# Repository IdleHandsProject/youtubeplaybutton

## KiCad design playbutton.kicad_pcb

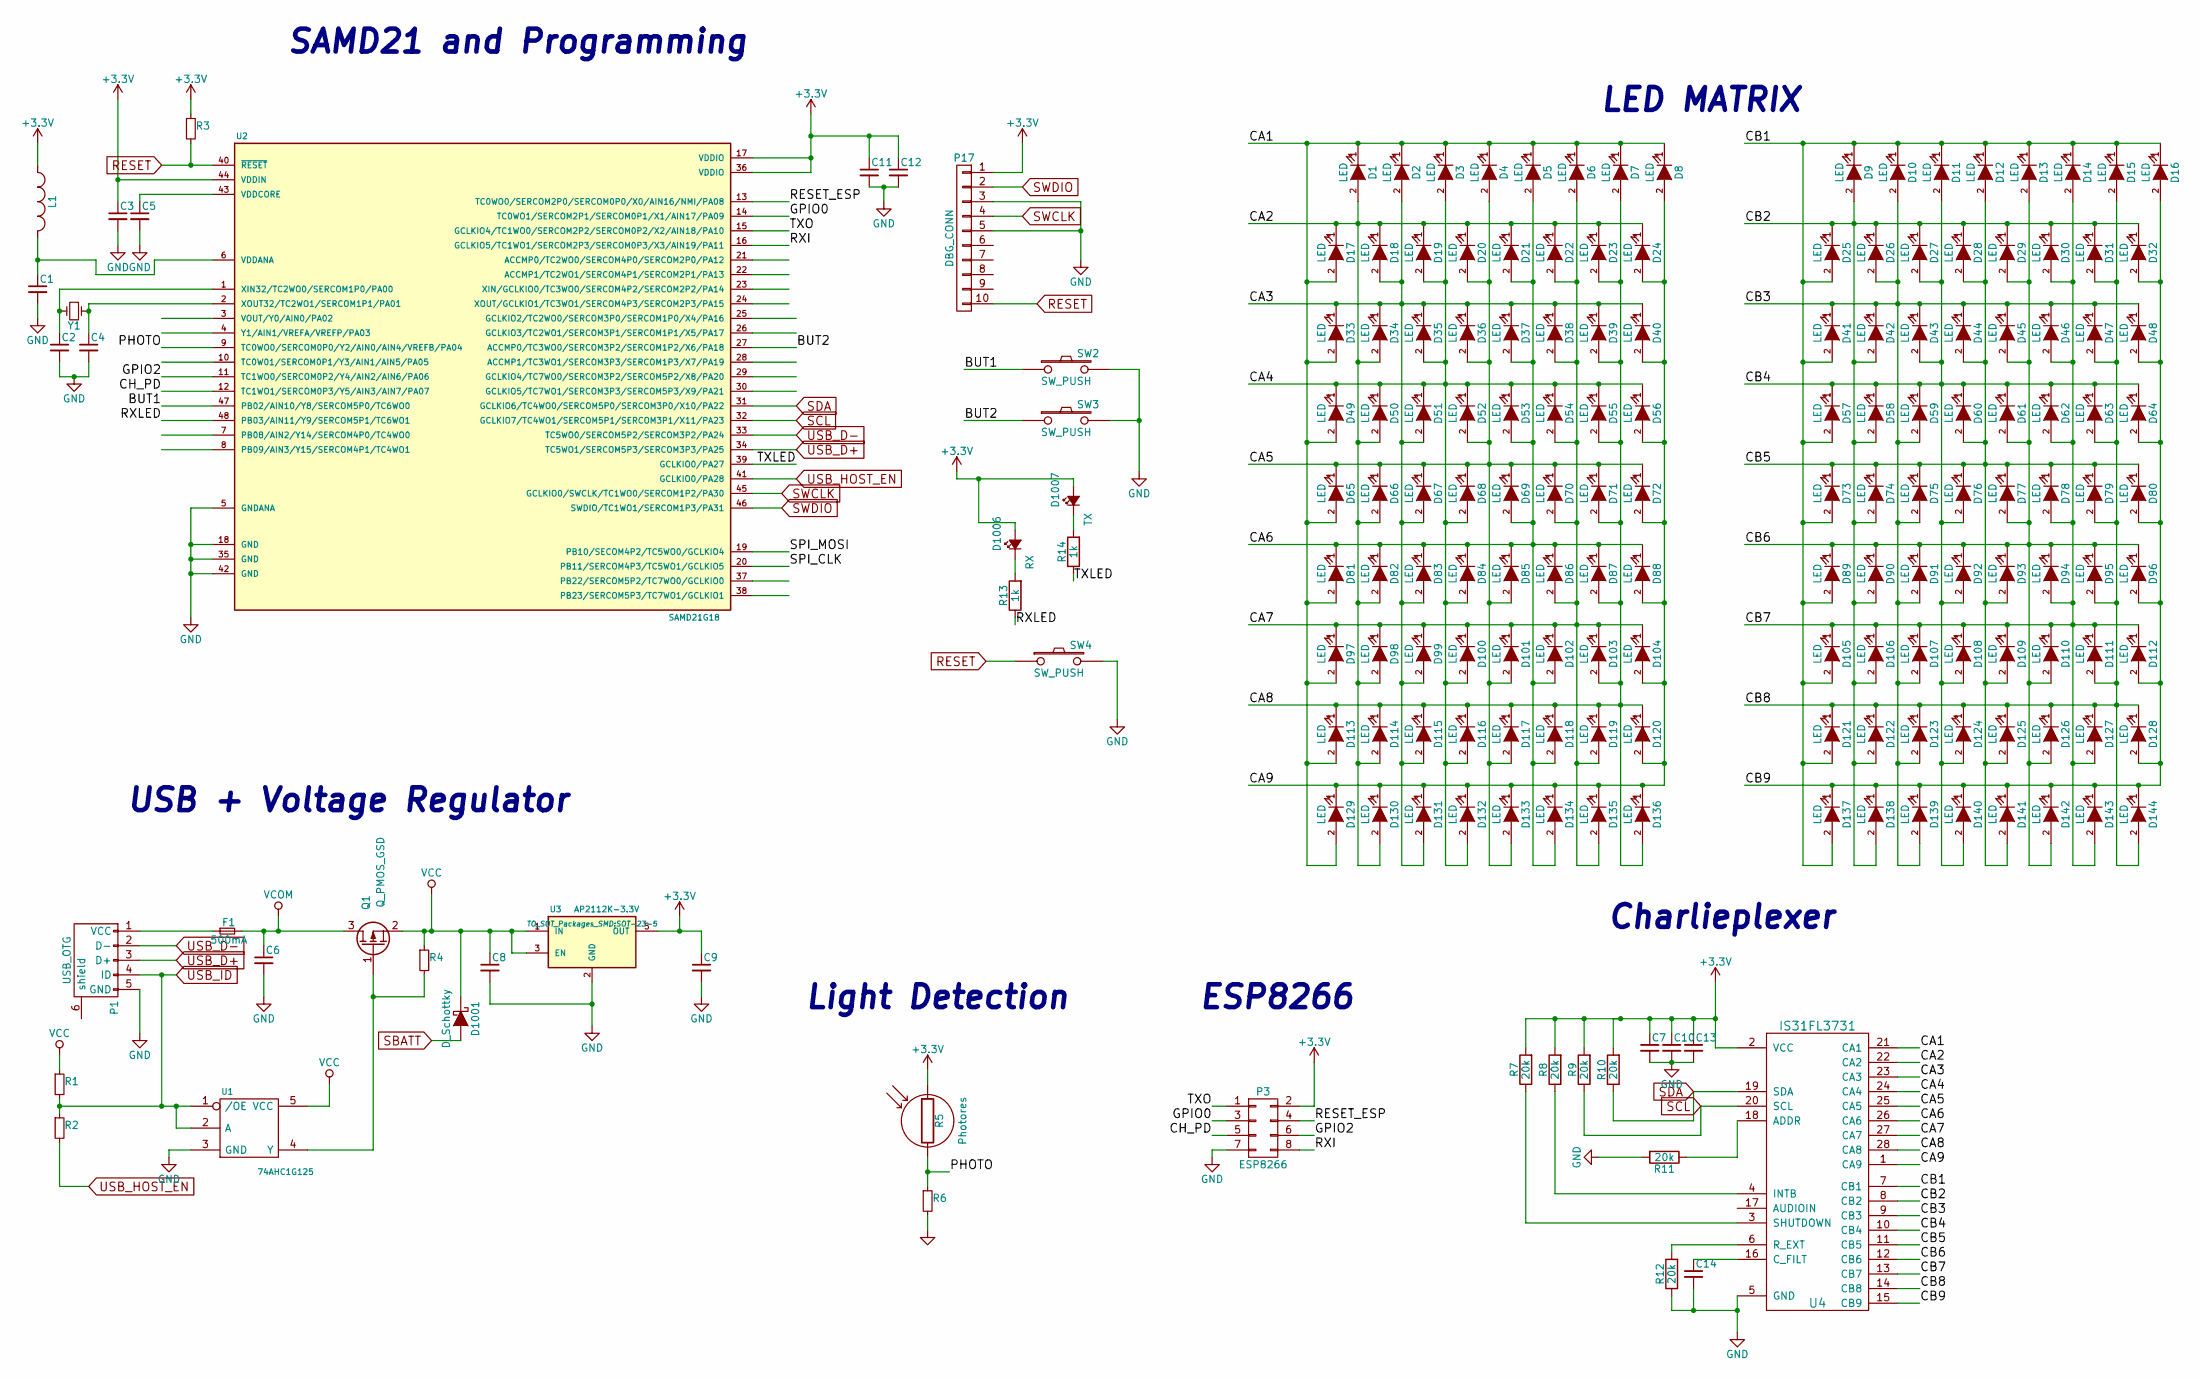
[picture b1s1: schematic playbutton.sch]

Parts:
C1, C3, C5, C11, C12, C13, C14: 0.1uF; C_0402_Hand; Digikey Part No. 490-6328-1-ND
C2, C4: 15pF; C_0402_Hand; Digikey Part No. 712-1261-1-ND
C6: 2.2uF; c_1206; Digikey Part No. 1276-1291-1-ND
C7, C10: 10uF; C_SM0603; Digikey Part No. 490-6405-1-ND
C8: 1uF; C_0402_Hand; Digikey Part No. 490-4516-1-ND
C9: 2.2uF; C_0402_Hand; Digikey Part No. 587-1059-1-ND
D1, D2, D3, D4, D5, D6, D7, D8, D9, D10, D11, D12, D13, D14, D15, D16, D17, D18, D19, D20, D21, D22, D23, D24, D25, D26, D27, D28, D29, D30, D31, D32, D33, D34, D35, D36, D37, D38, D39, D40, D41, D42, D43, D44, D45, D46, D47, D48, D49, D50, D51, D52, D53, D54, D55, D56, D57, D58, D59, D60, D61, D62, D63, D64, D65, D66, D67, D68, D69, D70, D71, D72, D73, D74, D75, D76, D77, D78, D79, D80, D81, D82, D83, D84, D85, D86, D87, D88, D89, D90, D91, D92, D93, D94, D95, D96, D97, D98, D99, D100, D101, D102, D103, D104, D105, D106, D107, D108, D109, D110, D111, D112, D113, D114, D115, D116, D117, D118, D119, D120, D121, D122, D123, D124, D125, D126, D127, D128, D129, D130, D131, D132, D133, D134, D135, D136, D137, D138, D139, D140, D141, D142, D143, D144: LED; Led_0603
D1001: D_Schottky; sod80c
D1006: RX; Led_0603; Digikey Part No. 160-1447-1-ND
D1007: TX; Led_0603; Digikey Part No. 160-1448-1-ND
F1: 500mA; c_1206; Digikey Part No. 507-1803-1-ND
L1: FB - 30Ohm; R_SM0603; Digikey Part No. 445-2986-1-ND
P1: USB_OTG; USB_Micro-B; Digikey Part No. 609-4618-1-ND
P3: ESP8266; Pin_Header_Straight_2x04
P17: DBG_CONN; Pin_Header_Straight_2x05_Pitch1.27mm; Digikey Part No. 1175-1627-ND
Q1: Q_PMOS_GSD; SOT23
R1: 100k; R_0402_Hand; Digikey Part No. 311-100KLRCT-ND
R2: 330; R_0402_Hand; Digikey Part No. 311-330JRCT-ND
R3, R6: 10k; R_0402_Hand; Digikey Part No. 311-10KJRCT-ND
R4: 47K; R_0402_Hand; Digikey Part No. 311-47.0KLRCT-ND
R5: Photores; Pin_Header_Straight_1x02
R7, R8, R9, R10, R11, R12: 20k; R_0402_Hand; Digikey Part No. 311-20KJRCT-ND
R13, R14: 1k; R_0402_Hand; Digikey Part No. 311-1.0KJRCT-ND
SW2: SW_PUSH; SW_SPST_PTS645; Digikey Part No. CKN9112CT-ND
SW3: SW_PUSH; SW_SPST_PTS645; Digikey Part No. CKN9084CT-ND
SW4: SW_PUSH; SW_SPST_EVQPE1; Digikey Part No. CKN9084CT-ND
U1: 74AHC1G125; sot23-5; Digikey Part No. 568-4452-1-ND
U2: SAMD21G18; TQFP-48_7x7mm_Pitch0.5mm; Digikey Part No. ATSAMD21G18A-AU-ND
U3: AP2112K-3.3V; SOT-23-5; Digikey Part No. AP2112K-3.3TRG1DICT-ND
U4: IS31FL3731; QFN-28-1EP_4x4mm_Pitch0.4mm
Y1: Crystal_Small; crystal_smd_5x3.2mm; Digikey Part No. 535-9536-1-ND

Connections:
+3V3: C3.1, C7.1, C9.1, C10.1, C11.1, C12.1, C13.1, D1006.2 (A), D1007.2 (A), L1.1, P3.2, P17.1, R3.1, R5.1, R7.2, R8.2, R9.2, R10.2, U2.17 (VDDIO), U2.36 (VDDIO), U2.44 (VDDIN), U3.5 (OUT), U4.2 (VCC)
/BUT1: SW2.1, U2.47 (PB02/AIN10/Y8/SERCOM5P0/TC6WO0)
/BUT2: SW3.1, U2.27 (ACCMP0/TC3WO0/SERCOM3P2/SERCOM1P2/X6/PA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)
/CA1: D1.1 (K), D2.1 (K), D3.1 (K), D4.1 (K), D5.1 (K), D6.1 (K), D7.1 (K), D8.1 (K), D17.2 (A), D33.2 (A), D49.2 (A), D65.2 (A), D81.2 (A), D97.2 (A), D113.2 (A), D129.2 (A), U4.21 (CA1)
/CA2: D1.2 (A), D17.1 (K), D18.1 (K), D19.1 (K), D20.1 (K), D21.1 (K), D22.1 (K), D23.1 (K), D24.1 (K), D34.2 (A), D50.2 (A), D66.2 (A), D82.2 (A), D98.2 (A), D114.2 (A), D130.2 (A), U4.22 (CA2)
/CA3: D2.2 (A), D18.2 (A), D33.1 (K), D34.1 (K), D35.1 (K), D36.1 (K), D37.1 (K), D38.1 (K), D39.1 (K), D40.1 (K), D51.2 (A), D67.2 (A), D83.2 (A), D99.2 (A), D115.2 (A), D131.2 (A), U4.23 (CA3)
/CA4: D3.2 (A), D19.2 (A), D35.2 (A), D49.1 (K), D50.1 (K), D51.1 (K), D52.1 (K), D53.1 (K), D54.1 (K), D55.1 (K), D56.1 (K), D68.2 (A), D84.2 (A), D100.2 (A), D116.2 (A), D132.2 (A), U4.24 (CA4)
/CA5: D4.2 (A), D20.2 (A), D36.2 (A), D52.2 (A), D65.1 (K), D66.1 (K), D67.1 (K), D68.1 (K), D69.1 (K), D70.1 (K), D71.1 (K), D72.1 (K), D85.2 (A), D101.2 (A), D117.2 (A), D133.2 (A), U4.25 (CA5)
/CA6: D5.2 (A), D21.2 (A), D37.2 (A), D53.2 (A), D69.2 (A), D81.1 (K), D82.1 (K), D83.1 (K), D84.1 (K), D85.1 (K), D86.1 (K), D87.1 (K), D88.1 (K), D102.2 (A), D118.2 (A), D134.2 (A), U4.26 (CA6)
/CA7: D6.2 (A), D22.2 (A), D38.2 (A), D54.2 (A), D70.2 (A), D86.2 (A), D97.1 (K), D98.1 (K), D99.1 (K), D100.1 (K), D101.1 (K), D102.1 (K), D103.1 (K), D104.1 (K), D119.2 (A), D135.2 (A), U4.27 (CA7)
/CA8: D7.2 (A), D23.2 (A), D39.2 (A), D55.2 (A), D71.2 (A), D87.2 (A), D103.2 (A), D113.1 (K), D114.1 (K), D115.1 (K), D116.1 (K), D117.1 (K), D118.1 (K), D119.1 (K), D120.1 (K), D136.2 (A), U4.28 (CA8)
/CA9: D8.2 (A), D24.2 (A), D40.2 (A), D56.2 (A), D72.2 (A), D88.2 (A), D104.2 (A), D120.2 (A), D129.1 (K), D130.1 (K), D131.1 (K), D132.1 (K), D133.1 (K), D134.1 (K), D135.1 (K), D136.1 (K), U4.1 (CA9)
/CB1: D9.1 (K), D10.1 (K), D11.1 (K), D12.1 (K), D13.1 (K), D14.1 (K), D15.1 (K), D16.1 (K), D25.2 (A), D41.2 (A), D57.2 (A), D73.2 (A), D89.2 (A), D105.2 (A), D121.2 (A), D137.2 (A), U4.7 (CB1)
/CB2: D9.2 (A), D25.1 (K), D26.1 (K), D27.1 (K), D28.1 (K), D29.1 (K), D30.1 (K), D31.1 (K), D32.1 (K), D42.2 (A), D58.2 (A), D74.2 (A), D90.2 (A), D106.2 (A), D122.2 (A), D138.2 (A), U4.8 (CB2)
/CB3: D10.2 (A), D26.2 (A), D41.1 (K), D42.1 (K), D43.1 (K), D44.1 (K), D45.1 (K), D46.1 (K), D47.1 (K), D48.1 (K), D59.2 (A), D75.2 (A), D91.2 (A), D107.2 (A), D123.2 (A), D139.2 (A), U4.9 (CB3)
/CB4: D11.2 (A), D27.2 (A), D43.2 (A), D57.1 (K), D58.1 (K), D59.1 (K), D60.1 (K), D61.1 (K), D62.1 (K), D63.1 (K), D64.1 (K), D76.2 (A), D92.2 (A), D108.2 (A), D124.2 (A), D140.2 (A), U4.10 (CB4)
/CB5: D12.2 (A), D28.2 (A), D44.2 (A), D60.2 (A), D73.1 (K), D74.1 (K), D75.1 (K), D76.1 (K), D77.1 (K), D78.1 (K), D79.1 (K), D80.1 (K), D93.2 (A), D109.2 (A), D125.2 (A), D141.2 (A), U4.11 (CB5)
/CB6: D13.2 (A), D29.2 (A), D45.2 (A), D61.2 (A), D77.2 (A), D89.1 (K), D90.1 (K), D91.1 (K), D92.1 (K), D93.1 (K), D94.1 (K), D95.1 (K), D96.1 (K), D110.2 (A), D126.2 (A), D142.2 (A), U4.12 (CB6)
/CB7: D14.2 (A), D30.2 (A), D46.2 (A), D62.2 (A), D78.2 (A), D94.2 (A), D105.1 (K), D106.1 (K), D107.1 (K), D108.1 (K), D109.1 (K), D110.1 (K), D111.1 (K), D112.1 (K), D127.2 (A), D143.2 (A), U4.13 (CB7)
/CB8: D15.2 (A), D31.2 (A), D47.2 (A), D63.2 (A), D79.2 (A), D95.2 (A), D111.2 (A), D121.1 (K), D122.1 (K), D123.1 (K), D124.1 (K), D125.1 (K), D126.1 (K), D127.1 (K), D128.1 (K), D144.2 (A), U4.14 (CB8)
/CB9: D16.2 (A), D32.2 (A), D48.2 (A), D64.2 (A), D80.2 (A), D96.2 (A), D112.2 (A), D128.2 (A), D137.1 (K), D138.1 (K), D139.1 (K), D140.1 (K), D141.1 (K), D142.1 (K), D143.1 (K), D144.1 (K), U4.15 (CB9)
/CH_PD: P3.5, U2.12 (TC1WO1/SERCOM0P3/Y5/AIN3/AIN7/PA07)
/GPIO0: P3.3, U2.14 (TC0WO1/SERCOM2P1/SERCOM0P1/X1/AIN17/PA09)
/GPIO2: P3.6, U2.11 (TC1WO0/SERCOM0P2/Y4/AIN2/AIN6/PA06)
/PHOTO: R5.2, R6.1, U2.9 (TC0WO0/SERCOM0P0/Y2/AIN0/AIN4/VREFB/PA04)
/RESET_ESP: P3.4, U2.13 (TC0WO0/SERCOM2P0/SERCOM0P0/X0/AIN16/NMI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)
/RXI: P3.8, U2.16 (GCLKIO5/TC1WO1/SERCOM2P3/SERCOM0P3/X3/A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)
/RXLED: R13.1, U2.48 (PB03/AIN11/Y9/SERCOM5P1/TC6WO1)
/SPI_CLK: U2.20 (PB11/SERCOM4P3/TC5WO1/GCLKIO5)
/SPI_MOSI: U2.19 (PB10/SECOM4P2/TC5WO0/GCLKIO4)
/TXLED: R14.1, U2.39 (GCLKIO0/PA27)
/TXO: P3.1, U2.15 (GCLKIO4/TC1WO0/SERCOM2P2/SERCOM0P2/X2/A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)
GND: C1.2, C2.2, C3.2, C4.2, C5.2, C6.2, C7.2, C8.2, C9.2, C10.2, C11.2, C12.2, C13.2, C14.2, P1.5 (GND), P3.7, P17.3, P17.5, R6.2, R11.2, R12.1, SW2.2, SW3.2, SW4.2, U1.3 (GND), U2.5 (GNDANA), U2.18 (GND), U2.35 (GND), U2.42 (GND), U3.2 (GND), U4.5 (GND)
unnamed: C1.1, L1.2, U2.6 (VDDANA)
unnamed: C2.1, U2.1 (XIN32/TC2WO0/SERCOM1P0/PA00), Y1.2
unnamed: C4.1, U2.2 (XOUT32/TC2WO1/SERCOM1P1/PA01), Y1.1
unnamed: C5.1, U2.43 (VDDCORE)
unnamed: C14.1, U4.16 (C_FILT)
unnamed: D1006.1 (K), R13.2
unnamed: D1007.1 (K), R14.2
unnamed: F1.1, P1.1 (VCC)
unnamed: Q1.1 (G), R4.2, U1.4 (Y)
unnamed: R7.1, U4.3 (SHUTDOWN)
unnamed: R8.1, U4.4 (INTB)
unnamed: R11.1, U4.18 (ADDR)
unnamed: R12.2, U4.6 (R_EXT)
RESET: P17.10, R3.2, SW4.1, U2.40 (~RESET~)
SCL: R9.1, U2.32 (GCLKIO7/TC4WO1/SERCOM5P1/SERCOM3P1/X11/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), U4.20 (SCL)
SDA: R10.1, U2.31 (GCLKIO6/TC4WO0/SERCOM5P0/SERCOM3P0/X10/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), U4.19 (SDA)
SWCLK: P17.4, U2.45 (GCLKIO0/SWCLK/TC1WO0/SERCOM1P2/PA30)
SWDIO: P17.2, U2.46 (SWDIO/TC1WO1/SERCOM1P3/PA31)
USB_D+: P1.3 (D+), U2.34 (TC5WO1/SERCOM5P3/SERCOM3P3/PA25)
USB_D-: P1.2 (D-), U2.33 (TC5WO0/SERCOM5P2/SERCOM3P2/PA24)
USB_HOST_EN: R2.2, U2.41 (GCLKIO0/PA28)
USB_ID: P1.4 (ID), R1.2, R2.1, U1.1 (/OE), U1.2 (A)
VCC: C8.1, D1001.1 (K), Q1.2 (S), R1.1, R4.1, U1.5 (VCC), U3.1 (IN), U3.3 (EN)
VCOM: C6.1, F1.2, Q1.3 (D)

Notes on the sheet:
USB + Voltage Regulator
LED MATRIX
ESP8266
Charlieplexer
Light Detection
SAMD21 and Programming

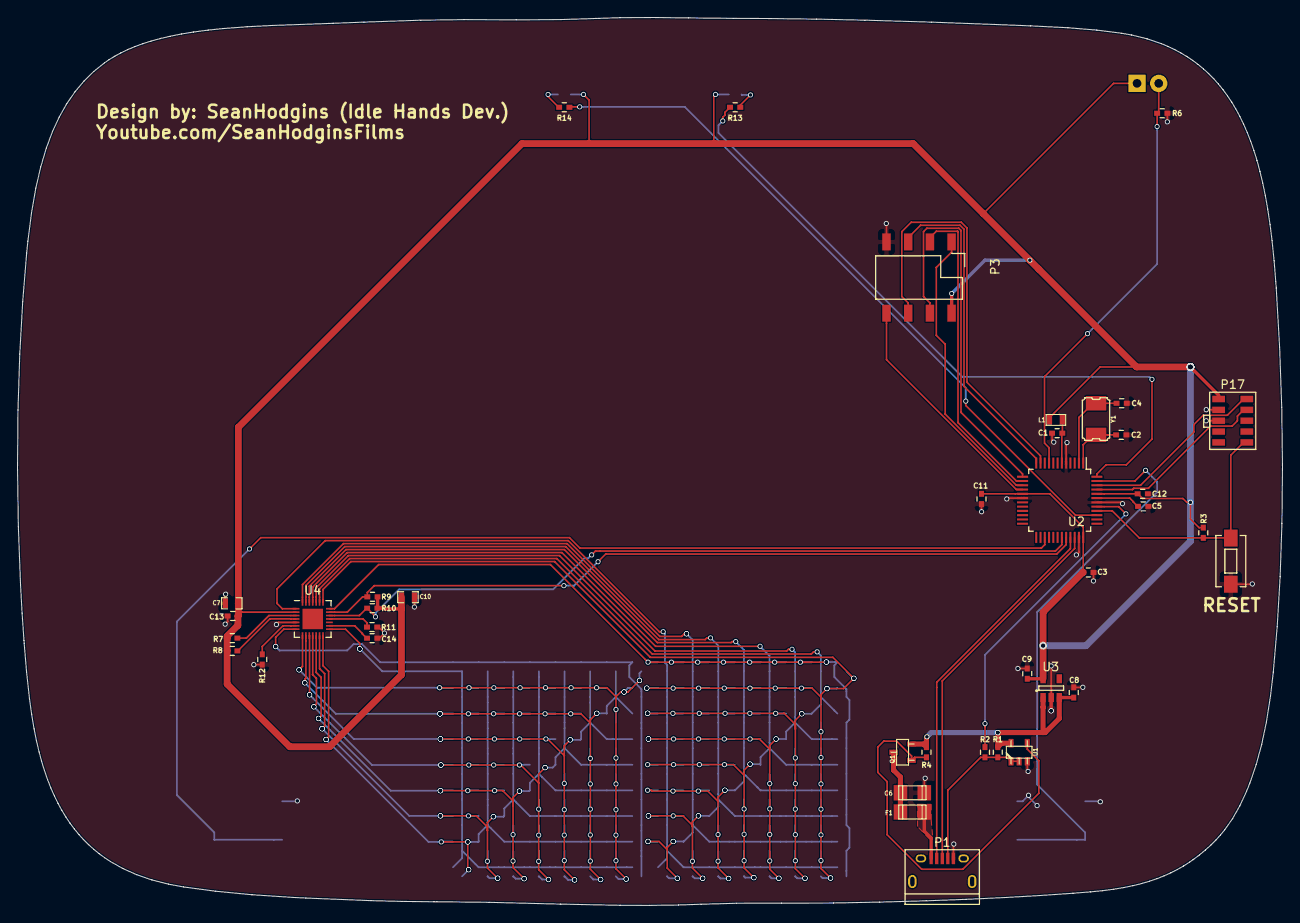
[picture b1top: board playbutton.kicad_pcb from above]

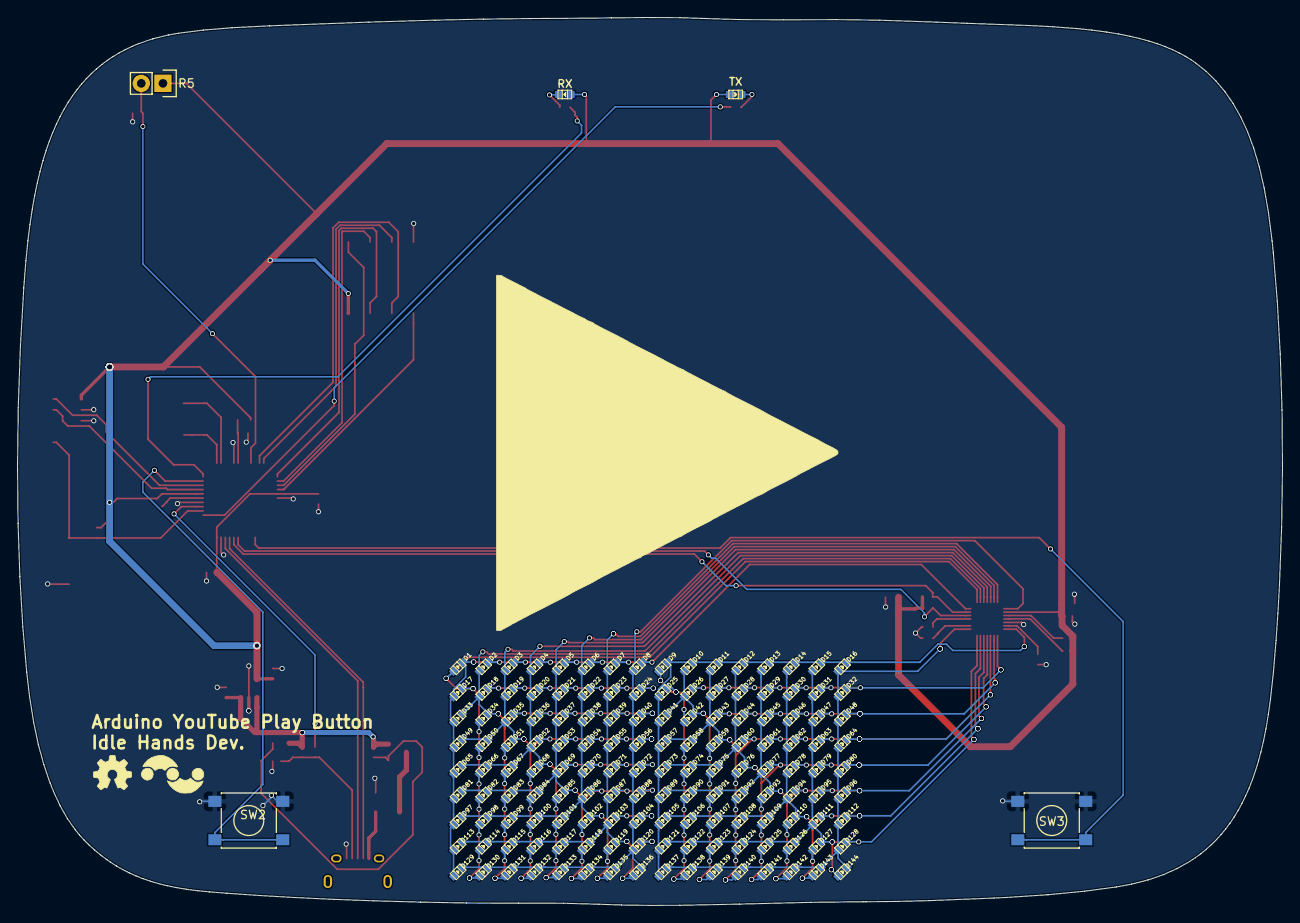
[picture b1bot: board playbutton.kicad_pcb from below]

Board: 2 copper layers, 148.1 x 103.9 mm, 188 parts (149 on the bottom side), 55 nets.

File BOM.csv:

ref,value,footprint,Digikey Part No.,Mouser Part No.,Quantity
C3 C5 C1 C11 C12 C14 C15,0.1uF,project_footprints:C_0402_Hand,490-6328-1-ND,,7
U5,DRV8835,project_footprints:WSON-12-2x3,296-30391-1-ND,,1
D1,BAT20J,project_footprints:sod80c,497-3381-1-ND,,1
U3,AP2112K-3.3V,TO_SOT_Packages_SMD:SOT-23-5,AP2112K-3.3TRG1DICT-ND,,1
C10,68uF,project_footprints:C_0402_Hand,P16816-1-ND,,1
P14 P15 P13,SONAR_2,Pin_Headers:Pin_Header_Straight_1x04,S5479-ND,,3
R3 R15 R17 R5 R6 R7 R8,10k,project_footprints:R_0402_Hand,311-10KJRCT-ND,,7
F1,500mA,project_footprints:c_1206,507-1803-1-ND,,1
C2 C4,15pF,project_footprints:C_0402_Hand,712-1261-1-ND,,2
SW2,SW_PUSH,project_footprints:SW_SPST_PTS645,CKN9112CT-ND,,1
SW3,SW_PUSH,project_footprints:SW_SPST_PTS645,CKN9084CT-ND,,1
D6,RX,project_footprints:Led_0603,160-1447-1-ND,,1
R2,330,project_footprints:R_0402_Hand,311-330JRCT-ND,,1
U1,74AHC1G125,project_footprints:sot23-5,568-4452-1-ND,,1
P1,USB_OTG,Connect:USB_Micro-B,609-4618-1-ND,,1
R1,100k,project_footprints:R_0402_Hand,311-100KLRCT-ND,,1
D7,TX,project_footprints:Led_0603,160-1448-1-ND,,1
C7,10uF,project_footprints:C_0402_Hand,311-1376-1-ND,,1
C8,1uF,project_footprints:C_0402_Hand,490-4516-1-ND,,1
C13,10uF,project_footprints:C_0402_Hand,311-1729-1-ND,,1
L2,47uH,project_footprints:I_1212,587-2104-1-ND,,1
Q1,Q_PMOS_DSG,project_footprints:SOT23,DMG2307L-7DICT-ND,,1
R4,47K,project_footprints:R_0402_Hand,311-47.0KLRCT-ND,,1
R14 R13,1k,project_footprints:R_0402_Hand,311-1.0KJRCT-ND,,2
U2,SAMD21G18,project_footprints:TQFP-48_7x7mm_Pitch0.5mm,ATSAMD21G18A-AU-ND,,1
P2,BatteryHolder,project_footprints:Battery_3xAAA_Holder,36-2479-ND,,1
CON1,MicroSD_Card,project_footprints:MicroSD_Card_Receptacle,114-00841-68-2-ND,,1
L1,FB - 30Ohm,project_footprints:R_SM0603,445-2986-1-ND,,1
C6 C9,2.2uF,project_footprints:C_0402_Hand,587-1059-1-ND,,2

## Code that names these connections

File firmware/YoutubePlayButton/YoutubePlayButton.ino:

#include <Wire.h>
#include <Adafruit_GFX.h>
#include <Adafruit_IS31FL3731.h>


#define DEBUG true
Adafruit_IS31FL3731 ledmatrix = Adafruit_IS31FL3731();



int GPIO0 = 3;
int ESP_RST = 4;
int CH_PD = 9;
int GPIO2 = 8;
int photocell = A3;
int but1 = A5;
int but2 = 10;
int pageTime = 3000;
String titleWord = "YouTube Play Button";
String Connect = "AT+CWJAP=";
String NETWORK = "XXXXXXXXXXXX"; ///Put your network name here
String PASS = "XXXXXXXXX";      ///Put network pass here



// The lookup table to make the brightness changes be more visible
uint8_t sweep[] = {1, 2, 3, 4, 6, 8, 10, 15, 20, 30, 40, 60, 60, 40, 30, 20, 15, 10, 8, 6, 4, 3, 2, 1};

void setup() {
  SerialUSB.begin(115200);
  Serial1.begin(115200);
  //while (!SerialUSB);

  pinMode(GPIO0, OUTPUT);
  pinMode(GPIO2, INPUT);
  pinMode(CH_PD, OUTPUT);
  pinMode(ESP_RST, INPUT_PULLUP);
  pinMode(photocell, INPUT);
  pinMode(but1, INPUT_PULLUP);
  pinMode(but2, INPUT_PULLUP);
  attachInterrupt(but2, esp_RST, FALLING);


  //esp_RST();

  digitalWrite(GPIO0, LOW);
  digitalWrite(CH_PD, LOW);
  delay(1000);
  digitalWrite(CH_PD, HIGH);
  //digitalWrite(ESP_RST, HIGH);

  
  ledmatrix.begin();
  ledmatrix.setTextSize(1);
  ledmatrix.setTextWrap(false);  // we dont want text to wrap so it scrolls nicely
  ledmatrix.setTextColor(50);
  ledmatrix.clear();
  ledmatrix.setCursor(0, 0);
  ledmatrix.print("AYPB");

                  sendData("AT+RST\r\n", 2000, DEBUG); // reset module
                  sendData("AT+CWMODE=3\r\n", 1000, DEBUG); // configure as access point

                  Connect += "\"";
                  Connect += NETWORK;
                  Connect += ",\"";
                  Connect += "\r\n";
                  sendData(Connect,10000,DEBUG);
                  sendData("AT+CIFSR\r\n", 1000, DEBUG); // get ip address
                  sendData("AT+CIPMUX=1\r\n", 1000, DEBUG); // configure for multiple connections
                  sendData("AT+CIPSERVER=1,80\r\n", 1000, DEBUG); // turn on server on port 80

                  randomSeed(analogRead(0));

                }

                  void loop() {
                  // animate over all the pixels, and set the brightness from the sweep table
                  //for (uint8_t incr = 0; incr < 24; incr++)
                  int x = random(15);
                  int y = random(7);
                  int x1 = random(15);
                  int y1 = random(7);

                  //checkConnect();
                  checkValue();


                  //ledmatrix.drawPixel(x, y, 255);
                  //pixelFlash(x,y);
                  //ledmatrix.drawChar(x,y,'a',255, 10, 5);
                  //ledmatrix.drawLine(x,y,x1,y1,105);
                  //delay(250);
                  //ledmatrix.drawLine(x,y,x1,y1,0);
                  //ledmatrix.fillScreen(10);
                  int bright = analogRead(photocell);
                  bright = map(bright, 1024, 0, 150, 10);

                  ledmatrix.setTextSize(1);
                  ledmatrix.setTextWrap(false);  // we dont want text to wrap so it scrolls nicely
                  ledmatrix.setTextColor(bright);
                  int displength = titleWord.length();
                  for (int8_t x = 18; x >= (-1*displength*6); x--) {
                  ledmatrix.clear();
                  ledmatrix.setCursor(x, 0);
                  ledmatrix.print(titleWord);
                  delay(50);
                }
                }

                  void pixelFlash(int x, int y) {
                  ledmatrix.drawPixel(x, y, 10);
                  ledmatrix.drawPixel(x, y, 20);
                  ledmatrix.drawPixel(x, y, 50);
                  ledmatrix.drawPixel(x, y, 100);
                  ledmatrix.drawPixel(x, y, 150);
                  ledmatrix.drawPixel(x, y, 200);
                  ledmatrix.drawPixel(x, y, 255);
                  ledmatrix.drawPixel(x, y, 255);
                  ledmatrix.drawPixel(x, y, 255);
                  ledmatrix.drawPixel(x, y, 200);
                  ledmatrix.drawPixel(x, y, 100);
                  ledmatrix.drawPixel(x, y, 50);
                  ledmatrix.drawPixel(x, y, 0);

                }

                  void esp_UART(){
                  if (SerialUSB.available()) // If data is sent to the monitor
                  {
                  String toSend = ""; // Create a new string
                  while (SerialUSB.available()) // While data is available
                  {
                  // Read from SerialUSB and add to the string:
                  toSend += (char)SerialUSB.read();
                }
                  // Print a message stating what we're sending:
                  //SerialUSB.print(toSend);

                  // Send the assembled string out over the hardware
                  // Serial1 port (TX pin 1).
                  Serial1.print(toSend);
}

if (Serial1.available()) // If data is sent from device
{
  String toSend = ""; // Create a new string
  while (Serial1.available()) // While data is available
  {
    // Read from hardware port and add to the string:
    toSend += (char)Serial1.read();
  }
  // Print a message stating what we've received:
  SerialUSB.print(toSend);
}
//delay(1000);
}

void esp_RST() {
  pinMode(ESP_RST, INPUT);
  pinMode(ESP_RST, OUTPUT);
  digitalWrite(ESP_RST, LOW);
  delay(100);
  titleWord = "RESET!!!";
  pinMode(ESP_RST, INPUT);
  delay(500);
}


void checkConnect() {
  if (Serial1.available()) // check if the esp is sending a message
  {
    /*
      while(Serial1.available())
      {
      // The esp has data so display its output to the serial window
      char c = Serial1.read(); // read the next character.
      SerialUSB.write(c);
      } */

    if (Serial1.find("+IPD,"))
    {
      delay(1000);

      int connectionId = Serial1.read() - 48; // subtract 48 because the read() function returns
      // the ASCII decimal value and 0 (the first decimal number) starts at 48

      String webpage = "<html><h1>Hello</h1><h2>World!</h2><button>LED1</button></html>";

      String cipSend = "AT+CIPSEND=";
      cipSend += connectionId;
      cipSend += ",";
      cipSend += webpage.length();
      cipSend += "\r\n";

      sendData(cipSend, pageTime, DEBUG);
      sendData(webpage, pageTime, DEBUG);

      webpage = "<html><button>LED2</button></html>";

      cipSend = "AT+CIPSEND=";
      cipSend += connectionId;
      cipSend += ",";
      cipSend += webpage.length();
      cipSend += "\r\n";

      sendData(cipSend, pageTime, DEBUG);
      sendData(webpage, pageTime, DEBUG);

      String closeCommand = "AT+CIPCLOSE=";
      closeCommand += connectionId; // append connection id
      closeCommand += "\r\n";

      sendData(closeCommand, 3000, DEBUG);
    }
  }
}

void checkValue() {
  if (Serial1.available()) // check if the esp is sending a message
  {

    /* while(Serial1.available())
      {
      // The esp has data so display its output to the serial window
      char c = Serial1.read(); // read the next character.
      SerialUSB.write(c);
      }
    */
    if (Serial1.find("+IPD,"))
    {
      delay(1000);

      int connectionId = Serial1.read() - 48; // subtract 48 because the read() function returns
      // the ASCII decimal value and 0 (the first decimal number) starts at 48
      //SerialUSB.print(connectionId);
      //int forwardslash = connectionId.indexOf('/');
      //int space = connectionId.indexOf(' ',forwardslash);
      //String subs = connectionId;
      //subs.remove(space);
      //subs.remove(1,forwardslash);
      //titleWord = subs;
      String webpage = "<html>Value Stored</html>";

      String cipSend = "AT+CIPSEND=";
      cipSend += connectionId;
      cipSend += ",";
      cipSend += webpage.length();
      cipSend += "\r\n";

      String subs = sendData(cipSend, pageTime, DEBUG);
      int forwardslash = subs.indexOf('/');
      int space = subs.indexOf(' ', forwardslash);

      subs.remove(space);
      subs.remove(0, forwardslash + 1);
      titleWord = subs;

      sendData(webpage, pageTime, DEBUG);

      String closeCommand = "AT+CIPCLOSE=0";
      //closeCommand += connectionId; // append connection id
      closeCommand += "\r\n";

      sendData(closeCommand, 3000, DEBUG);
    }
  }
}


String sendData(String command, const int timeout, boolean debug)
{
  String response = "";

  Serial1.print(command); // send the read character to the esp8266

  long int time = millis();

  while ( (time + timeout) > millis())
  {
    while (Serial1.available())
    {

      // The esp has data so display its output to the serial window
      char c = Serial1.read(); // read the next character.
      response += c;
    }
  }

  if (debug)
  {
    SerialUSB.print(response);
  }

  return response;
}

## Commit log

2016-11-22 Files Removed
2016-11-25 Added digikey part(s) No.
2016-11-25 Firmware Added
